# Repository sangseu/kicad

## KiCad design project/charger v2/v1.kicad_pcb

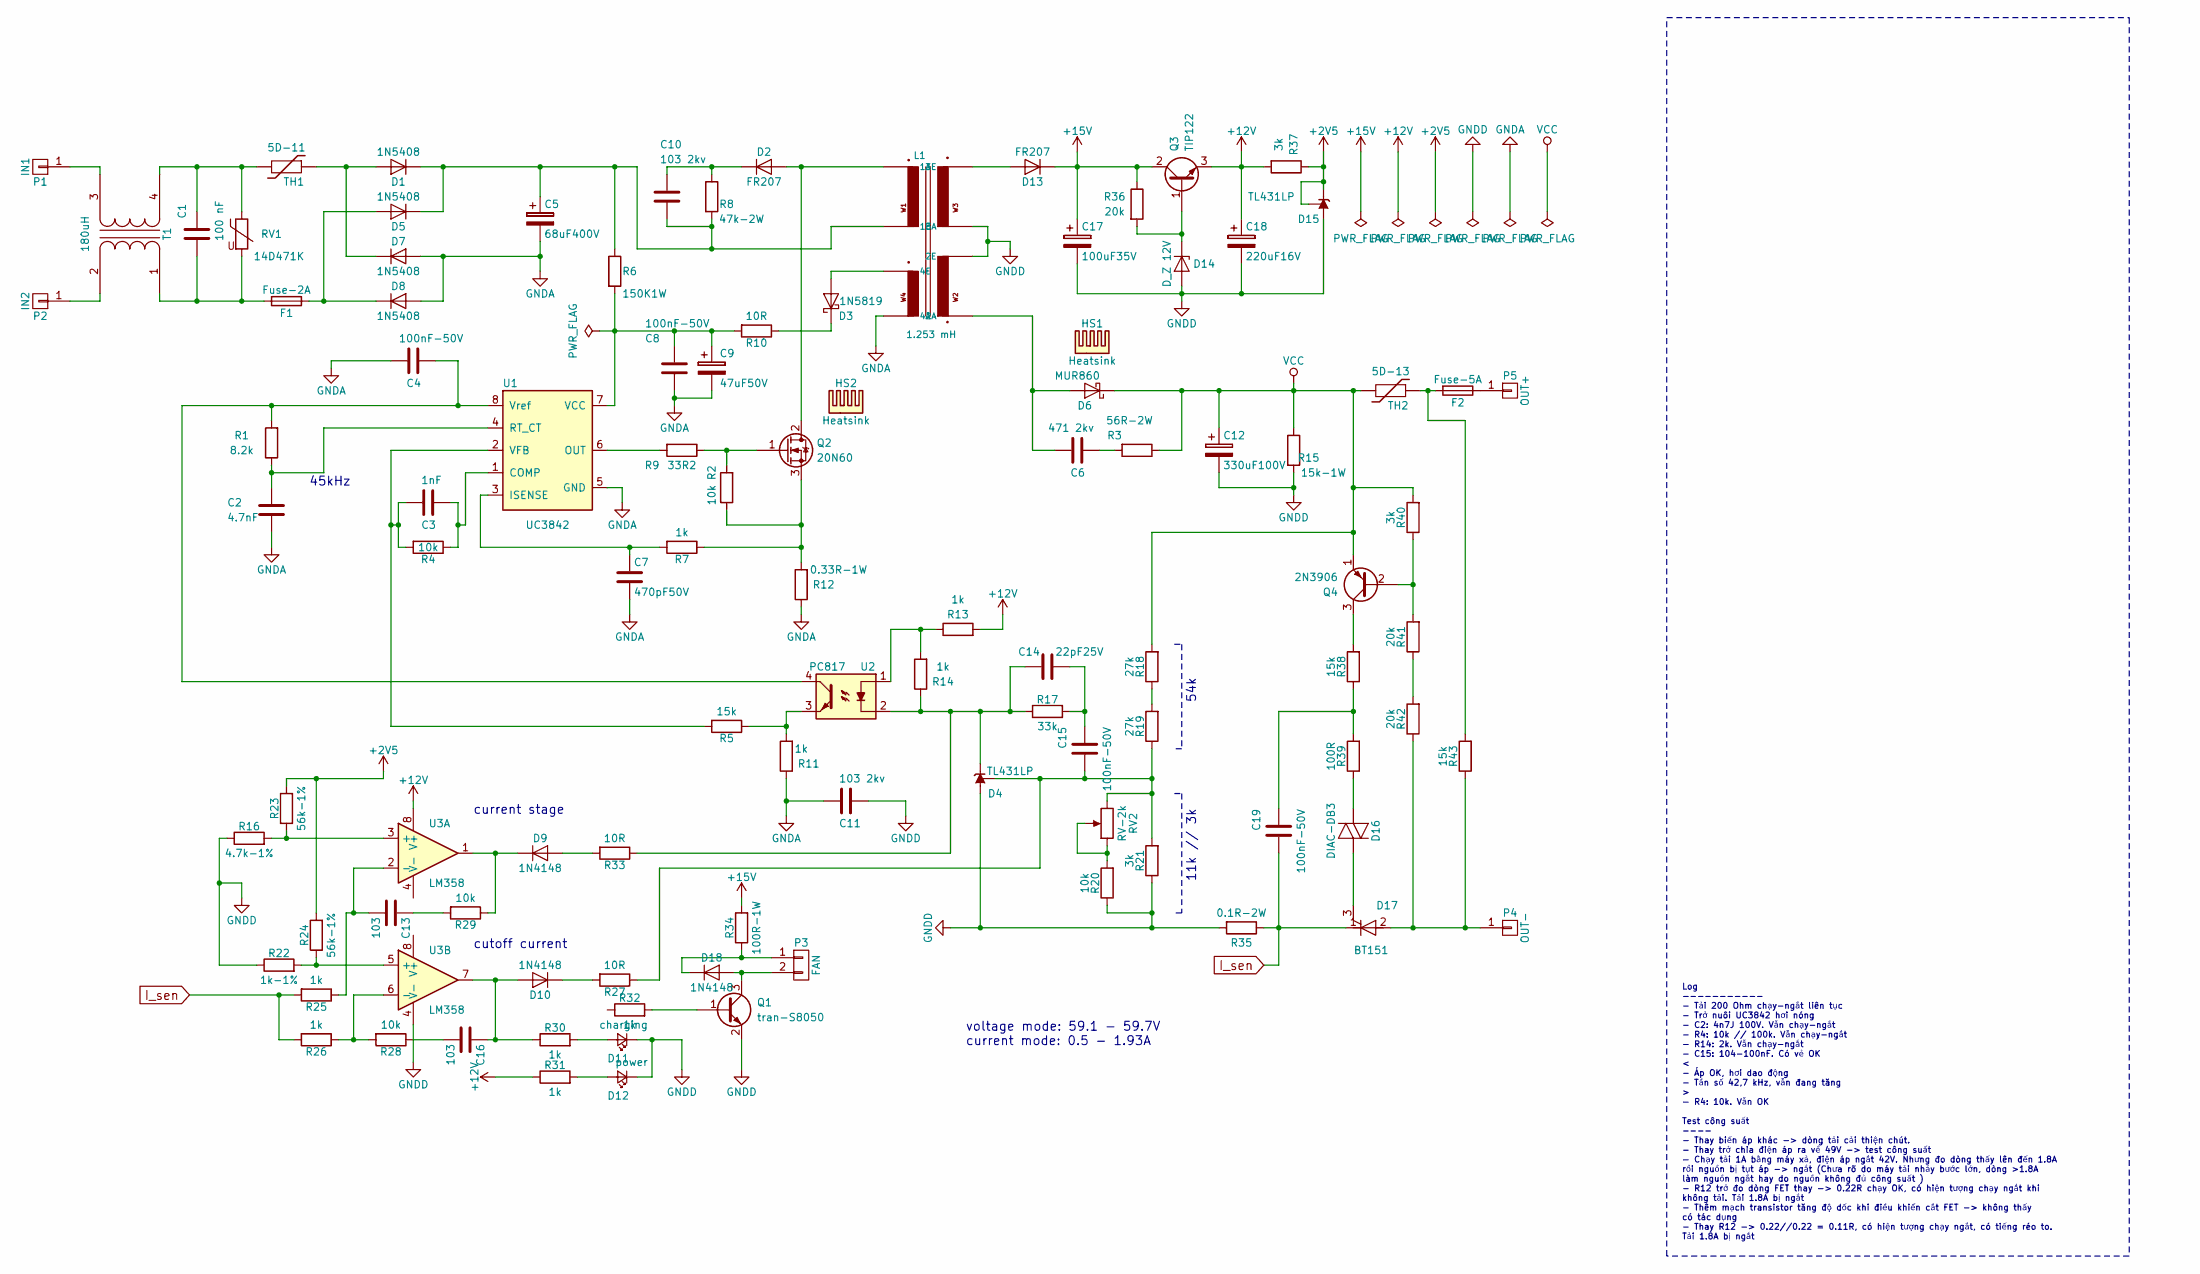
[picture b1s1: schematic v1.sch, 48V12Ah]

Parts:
C1: 100 nF; RV_Disc_D12_W4_P7.5
C2: 4.7nF; C_Rect_L7_W2.5_P5
C3: 1nF; C_0805_HandSoldering
C4, C8, C15, C19: 100nF-50V; C_Rect_L7_W2.5_P5
C5: 68uF400V; C_Radial_D18_L36_P7.5
C6: 471 2kv; C_Rect_L7_W2.5_P5
C7: 470pF50V; C_Rect_L7_W2.5_P5
C9: 47uF50V; C_Radial_D6.3_L11.2_P2.5
C10, C11: 103 2kv; C_Disc_D12_P7.75
C12: 330uF100V; C_Radial_D10_L21_P5
C13, C16: 103; C_Rect_L7_W2.5_P5
C14: 22pF25V; C_0805_HandSoldering
C17: 100uF35V; C_Radial_D6.3_L11.2_P2.5
C18: 220uF16V; C_Radial_D6.3_L11.2_P2.5
D1, D5, D7, D8: 1N5408; Diode_DO-201AD_Horizontal_RM15
D2, D13: FR207; Diode_DO-41_SOD81_Horizontal_RM10
D3: 1N5819; Diode_DO-41_SOD81_Horizontal_RM10
D4, D15: TL431LP; TO-92_Inline_Wide
D6: MUR860; Diode_TO-220_Vertical
D9, D10: 1N4148; Diode_DO-41_SOD81_Horizontal_RM10
D11: charging; LED-5MM
D12: power; LED-5MM
D14: D_Z 12V; Diode_DO-35_SOD27_Horizontal_RM10
D16: DIAC-DB3; Diode_DO-35_SOD27_Horizontal_RM10
D17: BT151; Diode_TO-220_Dual_CommonCathode_Vertical
D18: 1N4148; Diode_DO-41_SOD81_Vertical_AnodeUp
F1: Fuse-2A; Fuseholder5x20_horiz_open_inline_Type-I
F2: Fuse-5A; Fuseholder5x20_horiz_open_inline_Type-I
HS1, HS2: Heatsink; heatsink-D03PA
L1: 1.253 mH; trafo-siemens-RM8-12A
P1: IN1; MountingHole_2.2mm_M2_DIN965_Pad
P2: IN2; MountingHole_2.2mm_M2_DIN965_Pad
P3: FAN; Molex_KK-6410-02_02x2.54mm_Straight
P4: OUT-; MountingHole_2.2mm_M2_DIN965_Pad
P5: OUT+; MountingHole_2.2mm_M2_DIN965_Pad
Q1: tran-S8050; SOT-23
Q2: 20N60; TO-220_Neutral123_Vertical_LargePads
Q3: TIP122; TO-220_Neutral123_Vertical
Q4: 2N3906; TO-92_Inline_Wide
R1: 8.2k; R_0805_HandSoldering
R2, R4, R20, R28, R29: 10k; R_0805_HandSoldering
R3: 56R-2W; Resistor_Horizontal_RM15mm
R5: 15k; R_0805_HandSoldering
R6: 150K1W; Resistor_Horizontal_RM15mm
R7, R13, R25, R26, R30, R31, R32: 1k; Resistor_Horizontal_RM7mm
R8: 47k-2W; Resistor_Horizontal_RM15mm
R9: 33R2; Resistor_Horizontal_RM7mm
R10, R27, R33: 10R; R_0805_HandSoldering
R11, R14: 1k; R_0805_HandSoldering
R12: 0.33R-1W; Resistor_Horizontal_RM15mm
R15: 15k-1W; Resistor_Horizontal_RM15mm
R16: 4.7k-1%; R_0805_HandSoldering
R17: 33k; R_0805_HandSoldering
R18, R19: 27k; Resistor_Horizontal_RM7mm
R21, R40: 3k; R_0805_HandSoldering
R22: 1k-1%; Resistor_Horizontal_RM7mm
R23, R24: 56k-1%; Resistor_Horizontal_RM7mm
R34: 100R-1W; Resistor_Horizontal_RM10mm
R35: 0.1R-2W; Resistor_Horizontal_RM20mm
R36, R41: 20k; R_0805_HandSoldering
R37: 3k; Resistor_Horizontal_RM7mm
R38, R43: 15k; Resistor_Horizontal_RM7mm
R39: 100R; R_0805_HandSoldering
R42: 20k; Resistor_Horizontal_RM7mm
RV1: 14D471K; RV_Disc_D12_W3.9_P7.5
RV2: RV-2k; Potentiometer_Bourns_3296W_3-8Zoll_Inline_ScrewUp
T1: 180uH; inductors-MFE
TH1: 5D-11; R3
TH2: 5D-13; R3
U1: UC3842; DIP-8_W7.62mm_LongPads
U2: PC817; DIP-4_W7.62mm
U3: LM358; DIP-8_W7.62mm_LongPads

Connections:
+2V5: D15.1 (REF), D15.3 (K), R23.2, R24.2, R37.1
+12V: C18.1, Q3.3 (E), R13.2, R31.1, R37.2, U3.8 (V+)
+15V: C17.1, D13.1 (K), Q3.2 (C), R34.2, R36.1
GNDA: C2.2, C4.2, C5.2, C7.2, C8.2, C9.2, C11.2, D7.2 (A), D8.2 (A), L1.6 (4A), R11.1, R12.1, U1.5 (GND)
GNDD: C11.1, C12.2, C17.2, C18.2, D4.2 (A), D11.1 (K), D12.1 (K), D14.2 (A), D15.2 (A), L1.10 (2E), Q1.2 (E), R15.2, R16.1, R20.1, R21.1, R22.1, R35.2, U3.4 (V-)
I_sen: C19.1, D17.1 (K), R25.2, R26.2, R35.1
unnamed: C1.1, RV1.1, T1.4 (SB), TH1.2
unnamed: C1.2, F1.2, RV1.2, T1.1 (AA)
unnamed: C2.1, R1.1, U1.4 (RT_CT)
unnamed: C3.1, R4.1, U1.1 (COMP)
unnamed: C3.2, R4.2, R5.2, U1.2 (VFB)
unnamed: C4.1, R1.2, U1.8 (Vref), U2.4
unnamed: C6.1, R3.2
unnamed: C6.2, D6.2 (A), L1.8 (2A)
unnamed: C7.1, R7.2, U1.3 (ISENSE)
unnamed: C8.1, C9.1, R6.2, R10.2, U1.7 (VCC)
unnamed: C10.1, D2.1 (K), R8.1
unnamed: C5.1, C10.2, D1.1 (K), D5.1 (K), L1.3 (1E), R6.1, R8.2
unnamed: C13.1, R29.2
unnamed: C13.2, R25.1, U3.2 (-)
unnamed: C14.1, C15.2, R17.2
unnamed: C16.2, R28.1
unnamed: C19.2, R38.1, R39.2
unnamed: D1.2 (A), D7.1 (K), TH1.1
unnamed: D2.2 (A), L1.1 (1A), Q2.2 (D)
unnamed: D3.1 (K), R10.1
unnamed: D3.2 (A), L1.5 (4E)
unnamed: D5.2 (A), D8.1 (K), F1.1
unnamed: D9.1 (K), R29.1, U3.1
unnamed: D9.2 (A), R33.2
unnamed: D11.2 (A), R30.2
unnamed: D12.2 (A), R31.2
unnamed: D13.2 (A), L1.12 (3E)
unnamed: D14.1 (K), Q3.1 (B), R36.2
unnamed: D16.1 (K), R39.1
unnamed: D16.2 (A), D17.3 (G)
unnamed: D17.2 (A), P4.1, R42.1, R43.1
unnamed: D18.1 (K), P3.1, R34.1
unnamed: D18.2 (A), P3.2, Q1.3 (C)
unnamed: F2.1, P5.1
unnamed: F2.2, R43.2, TH2.1
unnamed: P1.1, T1.3 (SA)
unnamed: P2.1, T1.2 (AB)
unnamed: Q1.1 (B), R32.2
unnamed: Q2.1 (G), R2.2, R9.1
unnamed: Q2.3 (S), R2.1, R7.1, R12.2
unnamed: Q4.2 (B), R40.1, R41.2
unnamed: Q4.3 (C), R38.2
unnamed: R9.2, U1.6 (OUT)
unnamed: R5.1, R11.2, U2.3
unnamed: R13.1, R14.2, U2.1
unnamed: R16.2, R23.1, U3.3 (+)
unnamed: R18.1, R19.2
unnamed: R20.2, RV2.1, RV2.2
unnamed: R22.2, R24.1, U3.5 (+)
unnamed: R26.1, R28.2, U3.6 (-)
unnamed: R41.1, R42.2
VCC: C12.1, D6.1 (K), Q4.1 (E), R3.1, R15.1, R18.2, R40.2, TH2.2

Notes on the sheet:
voltage mode: 59.1 - 59.7V current mode: 0.5 - 1.93A
45kHz
current stage
cutoff current
54k
11k // 3k
Log ----------- - Tải 200 Ohm chạy-ngắt liên tục - Trở nuôi UC3842 hơi nóng - C2: 4n7J 100V. Vẫn chạy-ngắt - R4: 10k // 100k. Vẫn chạy-ngắt - R14: 2k. Vẫn chạy-ngắt - C15: 104-100nF. Có vẻ OK < - Áp OK, hơi dao động - Tần số 42,7 kHz, vẫn đang tăng > - R4: 10k. Vẫn OK Test công suất ---- - Thay biế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

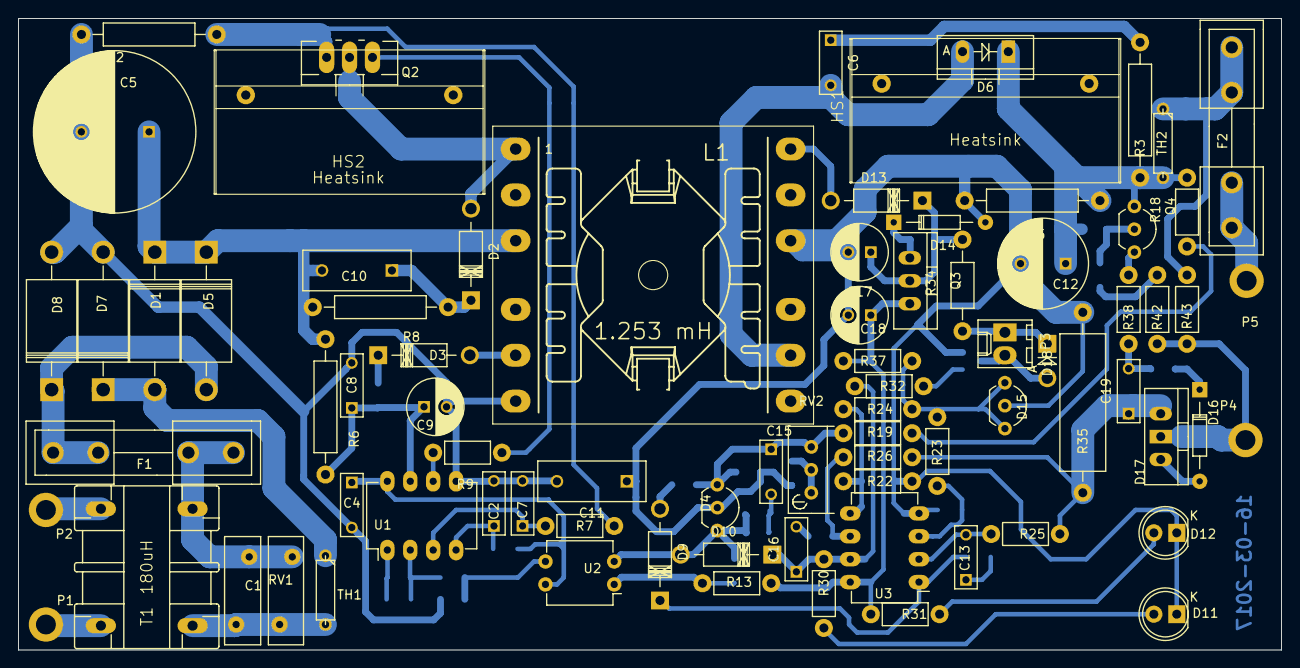
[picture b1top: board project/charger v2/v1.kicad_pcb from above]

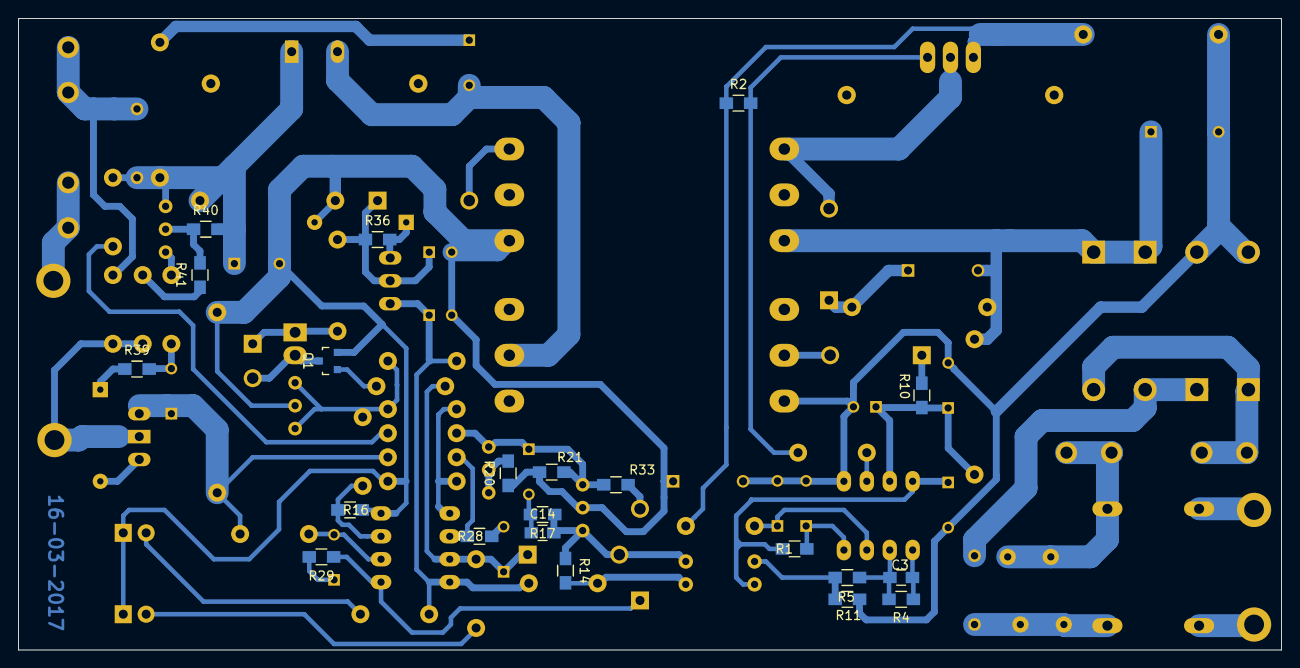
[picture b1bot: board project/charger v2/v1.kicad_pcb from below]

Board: 2 copper layers, 140.0 x 70.0 mm, 101 parts (21 on the bottom side), 61 nets.

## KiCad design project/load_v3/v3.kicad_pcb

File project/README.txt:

log
===
1. chager v1: so cap, phan hoi dien ap dung thong so. Mach dieu khien dong sac, dieu khien ngat sac SAI
2. 48V-1A: chay OK nhow su giup so cua anh Toan
3. 48V-2A. 48V-3A SAI

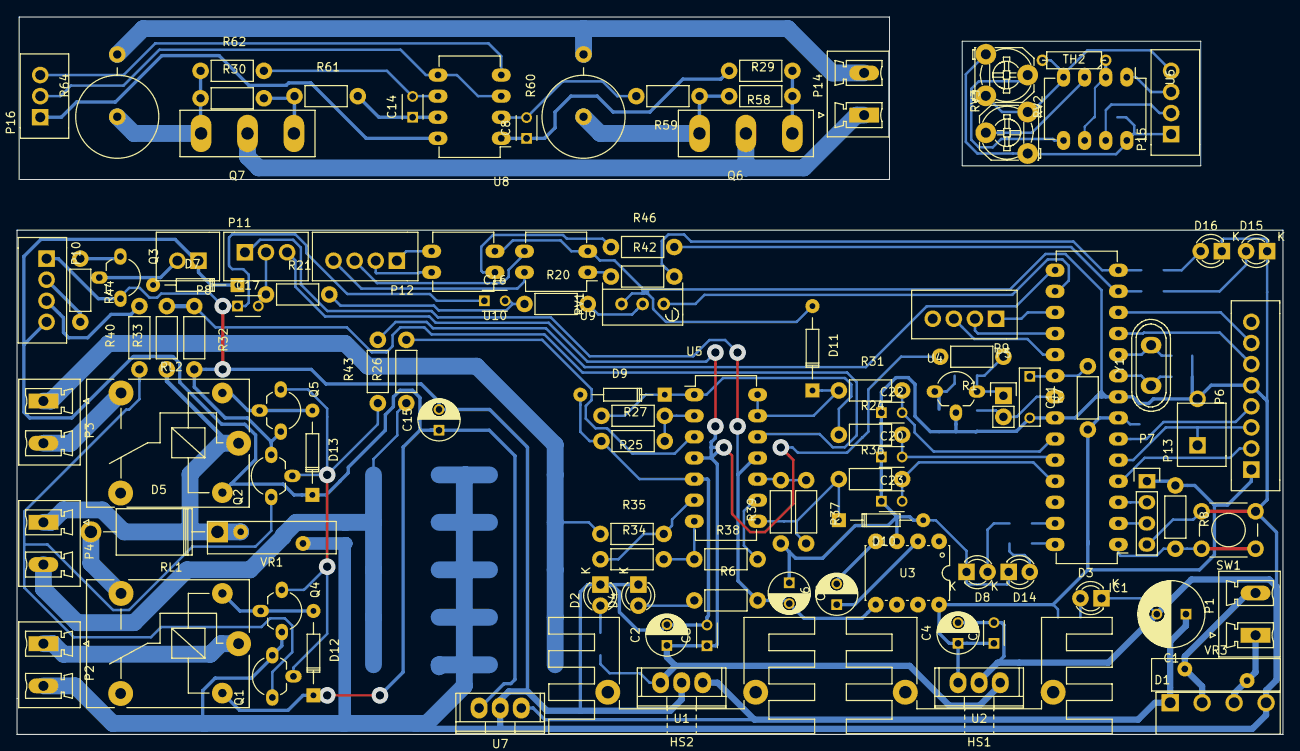
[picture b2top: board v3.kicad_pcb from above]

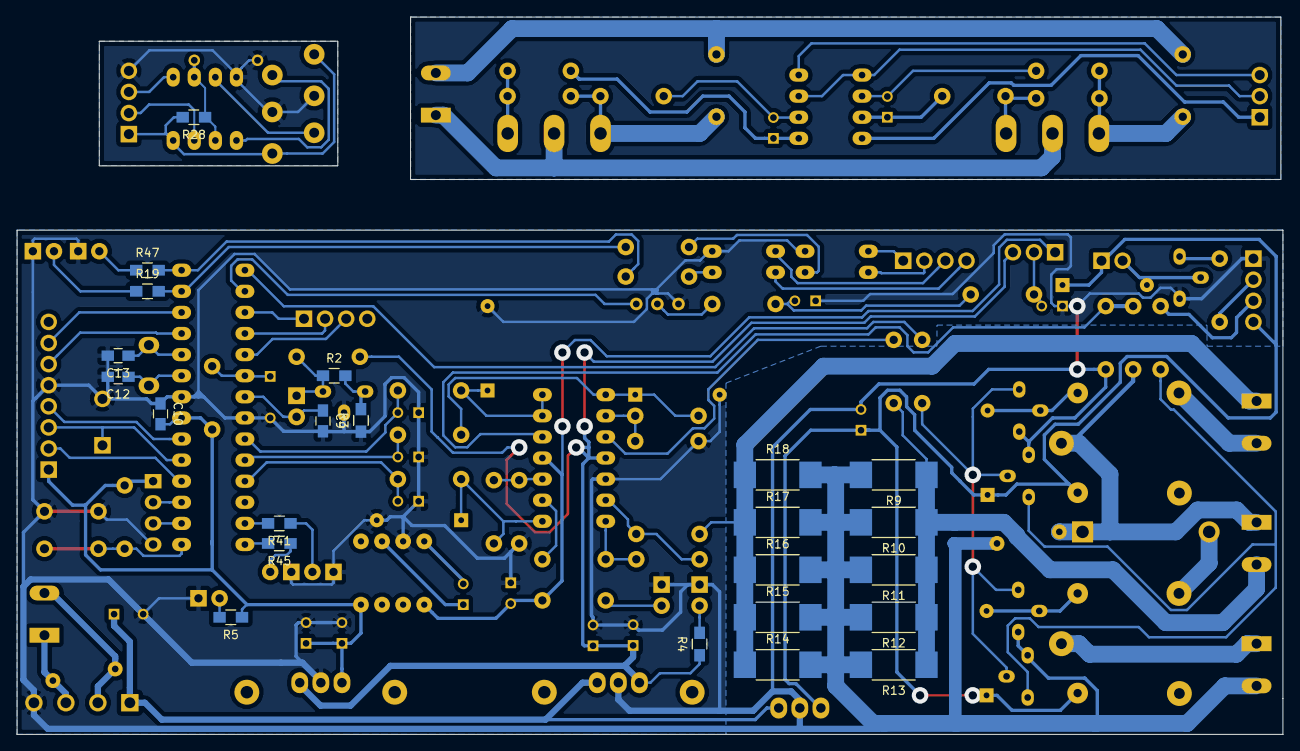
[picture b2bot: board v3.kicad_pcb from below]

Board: 2 copper layers, 152.4 x 60.7 mm, 132 parts (23 on the bottom side), 87 nets.

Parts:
C1: 220uF-50V; C_Radial_D8_L11.5_P3.5
C2, C15: 220F-25V; C_Radial_D5_L6_P2.5
C3, C5, C16, C17, C20, C22, C23: 100nF; C_Disc_D3_P2.5
C4: 470uF-25V; C_Radial_D5_L6_P2.5
C6, C7: 10uF-25V; C_Radial_D5_L6_P2.5
C8, C14: 22nF; C_Disc_D3_P2.5
C9, C10: 100nF; C_0805_HandSoldering
C11: 100nF; C_Rect_L7_W2.5_P5
C12, C13: 22pF; C_0805_HandSoldering
D1: Diode_Bridge; Diode_Bridge_KBP206
D2, D3, D4, D8, D14, D15, D16: Led_Small; LED-3MM
D5: 1N5402; Diode_DO-201AD_Horizontal_RM15
D7: 1N4001; Diode_DO-35_SOD27_Horizontal_RM10
D9, D10, D11: 5.1V; Diode_DO-35_SOD27_Horizontal_RM10
D12, D13: 4001; Diode_DO-35_SOD27_Horizontal_RM10
HS1, HS2: HEATSINK; Heatsink_Stonecold_HS-132_32x14mm_2xFixation1.5mm
IC1: ATMEGA328-P; DIP-28_W7.62mm_LongPads
P1: 12VAC; PhoenixContact_MCV-G_02x5.08mm_Vertical
P2: NGUON; PhoenixContact_MCV-G_02x5.08mm_Vertical
P3: SAC; PhoenixContact_MCV-G_02x5.08mm_Vertical
P4: DS; PhoenixContact_MCV-G_02x5.08mm_Vertical
P5: CONN_01X02; Pin_Header_Straight_1x02
P6: button; XH2.54-8P
P7: UART; Pin_Header_Straight_1x04
P8: FAN; XH2.54-2P
P9: 7-seg; XH2.54-4P
P10, P15: overheat; XH2.54-4P
P11: G; XH2.54-3P
P12: opto; XH2.54-4P
P13: tac_auto; XH2.54-2P
P14: pwr; PhoenixContact_MCV-G_02x5.08mm_Vertical
P16: g; XH2.54-3P
Q1, Q2, Q3: Q_NPN_BCE; TO-92_Molded_Wide_Oval_Reverse
Q4, Q5: 2n222; TO-92_Molded_Wide_Oval_Reverse
Q6, Q7: Q_NMOS_GDS; TO-247_Vertical_Neutral123
R1, R27, R39, R42, R43, R46, R59, R62: 1k; Resistor_Horizontal_RM7mm
R2, R3, R28: 10k; R_0805_HandSoldering
R4: 1k; R_0805_HandSoldering
R5, R19, R41, R45, R47: 470R; R_0805_HandSoldering
R6, R40, R44, R58, R61: 470R; Resistor_Horizontal_RM7mm
R7: 10uH; Resistor_Horizontal_RM7mm
R8, R20, R21, R26, R29, R30, R32, R34, R35, R38: 10k; Resistor_Horizontal_RM7mm
R9, R10, R11, R12, R13, R14, R15, R16, R17, R18: 0.5R; R_2512_HandSoldering
R24, R31, R36: 330R; Resistor_Horizontal_RM7mm
R25, R37: 8.2k; Resistor_Horizontal_RM7mm
R33: 180k; Resistor_Horizontal_RM7mm
R60, R64: 0.5R; Resistor_Vertical_RM7.5mm
RL1: onN; Relay_SANYOU_SRD_Series_Form_C
RL2: onS; Relay_SANYOU_SRD_Series_Form_C
RV1: 10k; Potentiometer_Bourns_3296W_3-8Zoll_Inline_ScrewUp
RV2, RV3: 20k; Potentiometer_Triwood_RM-065
SW1: reset; SW_PUSH_6mm
TH2: Thermistor; R3
U1, U7: LM7812CT; TO-220
U2: LM7805CT; TO-220
U3: ICL7660; PDIP-8
U4: TL431; TO-92_Molded_Wide_Oval_Reverse
U5: LM324N; DIP-14_W7.62mm_LongPads
U6, U8: LM358; DIP-8_W7.62mm_LongPads
U9, U10: PC817; DIP-4_W7.62mm_LongPads
VR1, VR3: 14D180V; RV_Disc_D15.5_W3.9_P7.5
Y1: 16MHz; Crystal_HC50-U_Vertical

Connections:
12Vrelay: C15.1, D7.1, D12.1, D13.1, P8.1, P10.4, P15.1, R28.2, RL1.5, RL2.5, RV2.1, RV3.1, U6.8, U7.3
17V: C1.1, D1.3, U1.1, U7.1
+5V: C4.1, C5.1, C10.2, IC1.7, P6.1, P7.1, R5.1, R7.1, R8.1, U2.3, U3.8
+12V: C2.1, C3.1, P11.3, P16.1, R1.2, R4.1, U1.3, U2.1, U5.4, U8.8
-5V: C7.2, P11.1, P16.3, R6.2, U3.5, U5.11, U8.4
D: D5.1, P4.1, P14.1, Q6.2, Q7.2, R33.1, RL2.1, VR1.1
G: C17.2, P11.2, P16.2, R21.1, U8.3, U8.5
N+: P2.1, RL1.1
N-: C1.2, C2.2, C3.2, C4.2, C5.2, C7.1, C9.2, C10.1, C11.2, C12.2, C13.2, C15.2, C16.1, C17.1, C20.1, C22.1, C23.1, D1.1, D2.1, D3.1, D4.1, D8.1, D9.2, D10.2, D11.2, D14.1, D15.1, D16.1, IC1.8, IC1.22, P2.2, P6.5, P7.4, P10.1, P13.2, P15.4, Q1.3, Q2.3, Q3.3, Q4.3, Q5.3, R3.1, R9.2, R10.2, R11.2, R12.2, R13.2, R14.2, R15.2, R16.2, R17.2, R18.2, R27.1, R32.2, R39.1, RV1.3, RV2.3, RV3.3, SW1.2, TH2.2, U1.2, U2.2, U3.3, U4.2, U5.5, U6.4, U7.2, U9.2, U10.2, VR1.2
unnamed: C6.1, U3.2
unnamed: C6.2, U3.4
unnamed: C8.1, R58.2, U8.1
unnamed: C8.2, R59.2, U8.2
unnamed: C11.1, IC1.20, R7.2
unnamed: C12.1, IC1.9, Y1.1
unnamed: C13.1, IC1.10, Y1.2
unnamed: C14.1, R61.2, U8.7
unnamed: C14.2, R62.2, U8.6
unnamed: C16.2, R20.1, R21.2
unnamed: D1.2, P1.2, VR3.2
unnamed: D1.4, P1.1, VR3.1
unnamed: D2.2, R4.2
unnamed: D3.2, R5.2
unnamed: D4.2, R6.1
unnamed: D7.2, P8.2, Q3.2
unnamed: D8.2, R41.1
unnamed: D9.1, R24.1, R25.2, U5.1
unnamed: D10.1, R36.1, R37.2, U5.8
unnamed: D11.1, R31.1, U5.13, U5.14
unnamed: D12.2, Q4.2, RL1.2
unnamed: D13.2, Q5.2, RL2.2
unnamed: D14.2, R45.1
unnamed: D15.2, R19.1
unnamed: D16.2, R47.1
unnamed: IC1.1, R8.2, SW1.1
unnamed: IC1.15, R43.2
unnamed: P5.1, R1.1, R2.1, U4.3
unnamed: P12.1, U10.3
unnamed: P12.2, U10.4
unnamed: P12.3, U9.3
unnamed: P12.4, U9.4
unnamed: Q1.1, Q2.1, R40.1
unnamed: Q3.1, R44.1
unnamed: Q6.1, R29.2, R58.1
unnamed: Q6.3, R29.1, R59.1, R60.1
unnamed: Q7.1, R30.2, R61.1
unnamed: Q7.3, R30.1, R62.1, R64.1
unnamed: R2.2, R3.2, U4.1
unnamed: R20.2, RV1.2
unnamed: R25.1, R27.2, U5.2
unnamed: R26.2, U5.3
unnamed: R28.1, TH2.1, U6.2, U6.6
unnamed: R32.1, R33.2, U5.12
unnamed: R34.1, R35.2, U5.6
unnamed: R34.2, R38.1, U5.7
unnamed: R37.1, R39.2, U5.10
unnamed: R38.2, U5.9
unnamed: RV2.2, U6.5
unnamed: RV3.2, U6.3
RX: IC1.2, P7.3
S: P4.2, P14.2, R9.1, R10.1, R11.1, R12.1, R13.1, R26.1, R60.2, R64.2
S+: P3.2, RL2.3
S-: P3.1, R14.1, R15.1, R16.1, R17.1, R18.1, R35.1
TX: IC1.3, P7.2
Vref: C9.1, IC1.21, P5.2
buzz: IC1.12, P6.7
down: IC1.11, P6.6
fail: IC1.28, R45.2
l_auto: IC1.13, R19.2, R46.2
l_start: IC1.14, R42.2, R47.2
off: P10.3, P15.2, R40.2, U6.7
ok: IC1.27, R41.2
onFan: P10.2, P15.3, R44.2, U6.1
onN: Q1.2, Q2.2, Q4.1, Q5.1, R43.1
opto_auto: R46.1, U10.1
opto_start: R42.1, U9.1
pwm: IC1.16, RV1.1
rN+: D5.2, RL1.3
rck: IC1.19, P9.3
scr: IC1.18, P9.2
senIN: C20.2, IC1.24, R24.2
senIS: C23.2, IC1.25
senUS: C22.2, IC1.23, R31.2
ser: IC1.17, P9.1
start: IC1.5, P6.3, P13.1
stop: IC1.4, P6.2
up: IC1.6, P6.4

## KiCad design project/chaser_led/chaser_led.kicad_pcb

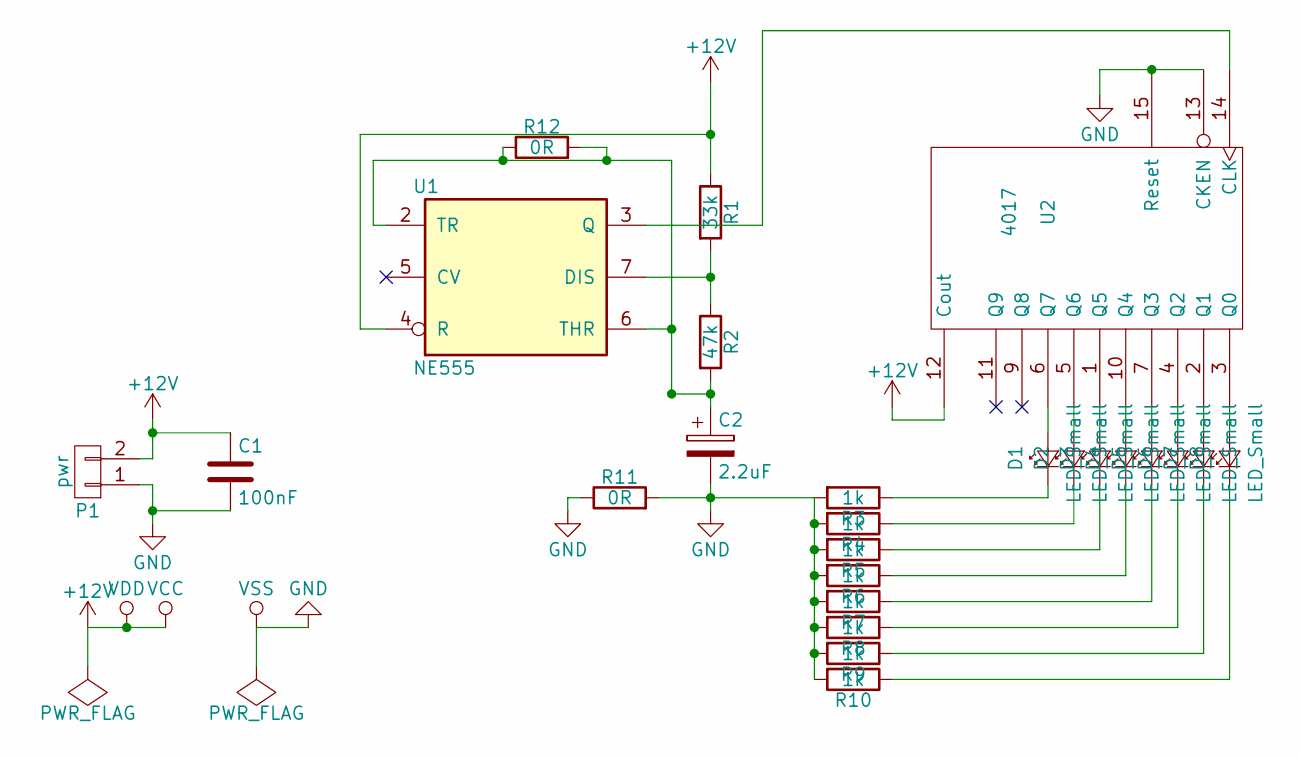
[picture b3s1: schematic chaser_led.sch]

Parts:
C1: 100nF; C_Disc_D3_P2.5
C2: 2.2uF; C_Radial_D5_L6_P2.5
D1, D2, D3, D4, D5, D6, D7, D8: LED_Small; LED-3MM
P1: pwr; AK300-2
R1: 33k; Resistor_Horizontal_RM7mm
R2: 47k; Resistor_Horizontal_RM7mm
R3, R4, R5, R6, R7, R8, R9, R10: 1k; Resistor_Horizontal_RM7mm
R11, R12: 0R; WireConnection_0.80mmDrill
U1: NE555; SOIC-8-N
U2: 4017; SO-16-N

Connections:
+12V: C1.1, P1.2, R1.1, U1.4 (R), U1.8 (VCC), U2.12 (Cout), U2.16 (VDD)
GND: C1.2, C2.2, P1.1, R3.2, R4.2, R5.2, R6.2, R7.2, R8.2, R9.2, R10.2, R11.1, R11.2, U1.1 (GND), U2.8 (VSS), U2.13 (CKEN), U2.15 (Reset)
unnamed: C2.1, R2.2, R12.1, R12.2, U1.2 (TR), U1.6 (THR)
unnamed: D1.1 (K), R3.1
unnamed: D1.2 (A), U2.6 (Q7)
unnamed: D2.1 (K), R4.1
unnamed: D2.2 (A), U2.5 (Q6)
unnamed: D3.1 (K), R5.1
unnamed: D3.2 (A), U2.1 (Q5)
unnamed: D4.1 (K), R6.1
unnamed: D4.2 (A), U2.10 (Q4)
unnamed: D5.1 (K), R7.1
unnamed: D5.2 (A), U2.7 (Q3)
unnamed: D6.1 (K), R8.1
unnamed: D6.2 (A), U2.4 (Q2)
unnamed: D7.1 (K), R9.1
unnamed: D7.2 (A), U2.2 (Q1)
unnamed: D8.1 (K), R10.1
unnamed: D8.2 (A), U2.3 (Q0)
unnamed: R1.2, R2.1, U1.7 (DIS)
unnamed: U1.3 (Q), U2.14 (CLK)

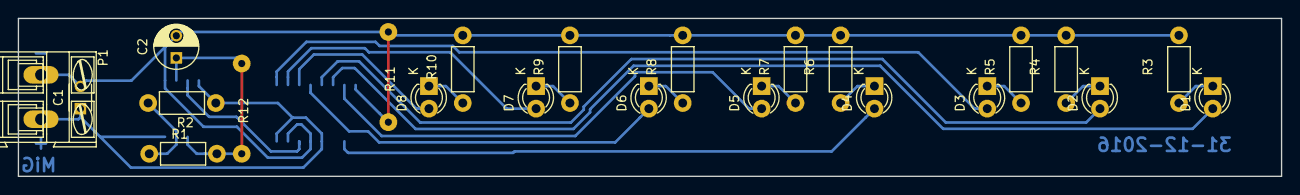
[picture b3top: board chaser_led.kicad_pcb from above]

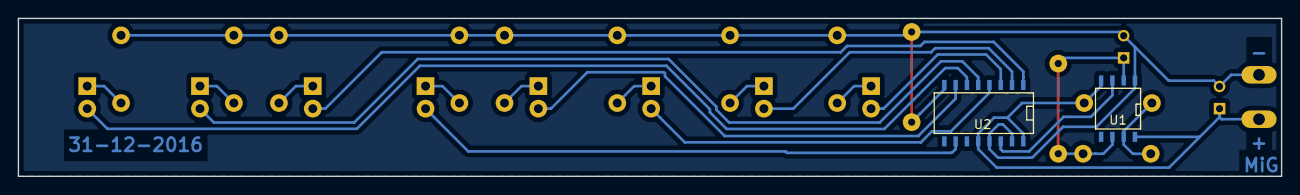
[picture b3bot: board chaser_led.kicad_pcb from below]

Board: 2 copper layers, 142.2 x 17.8 mm, 25 parts (2 on the bottom side), 21 nets.

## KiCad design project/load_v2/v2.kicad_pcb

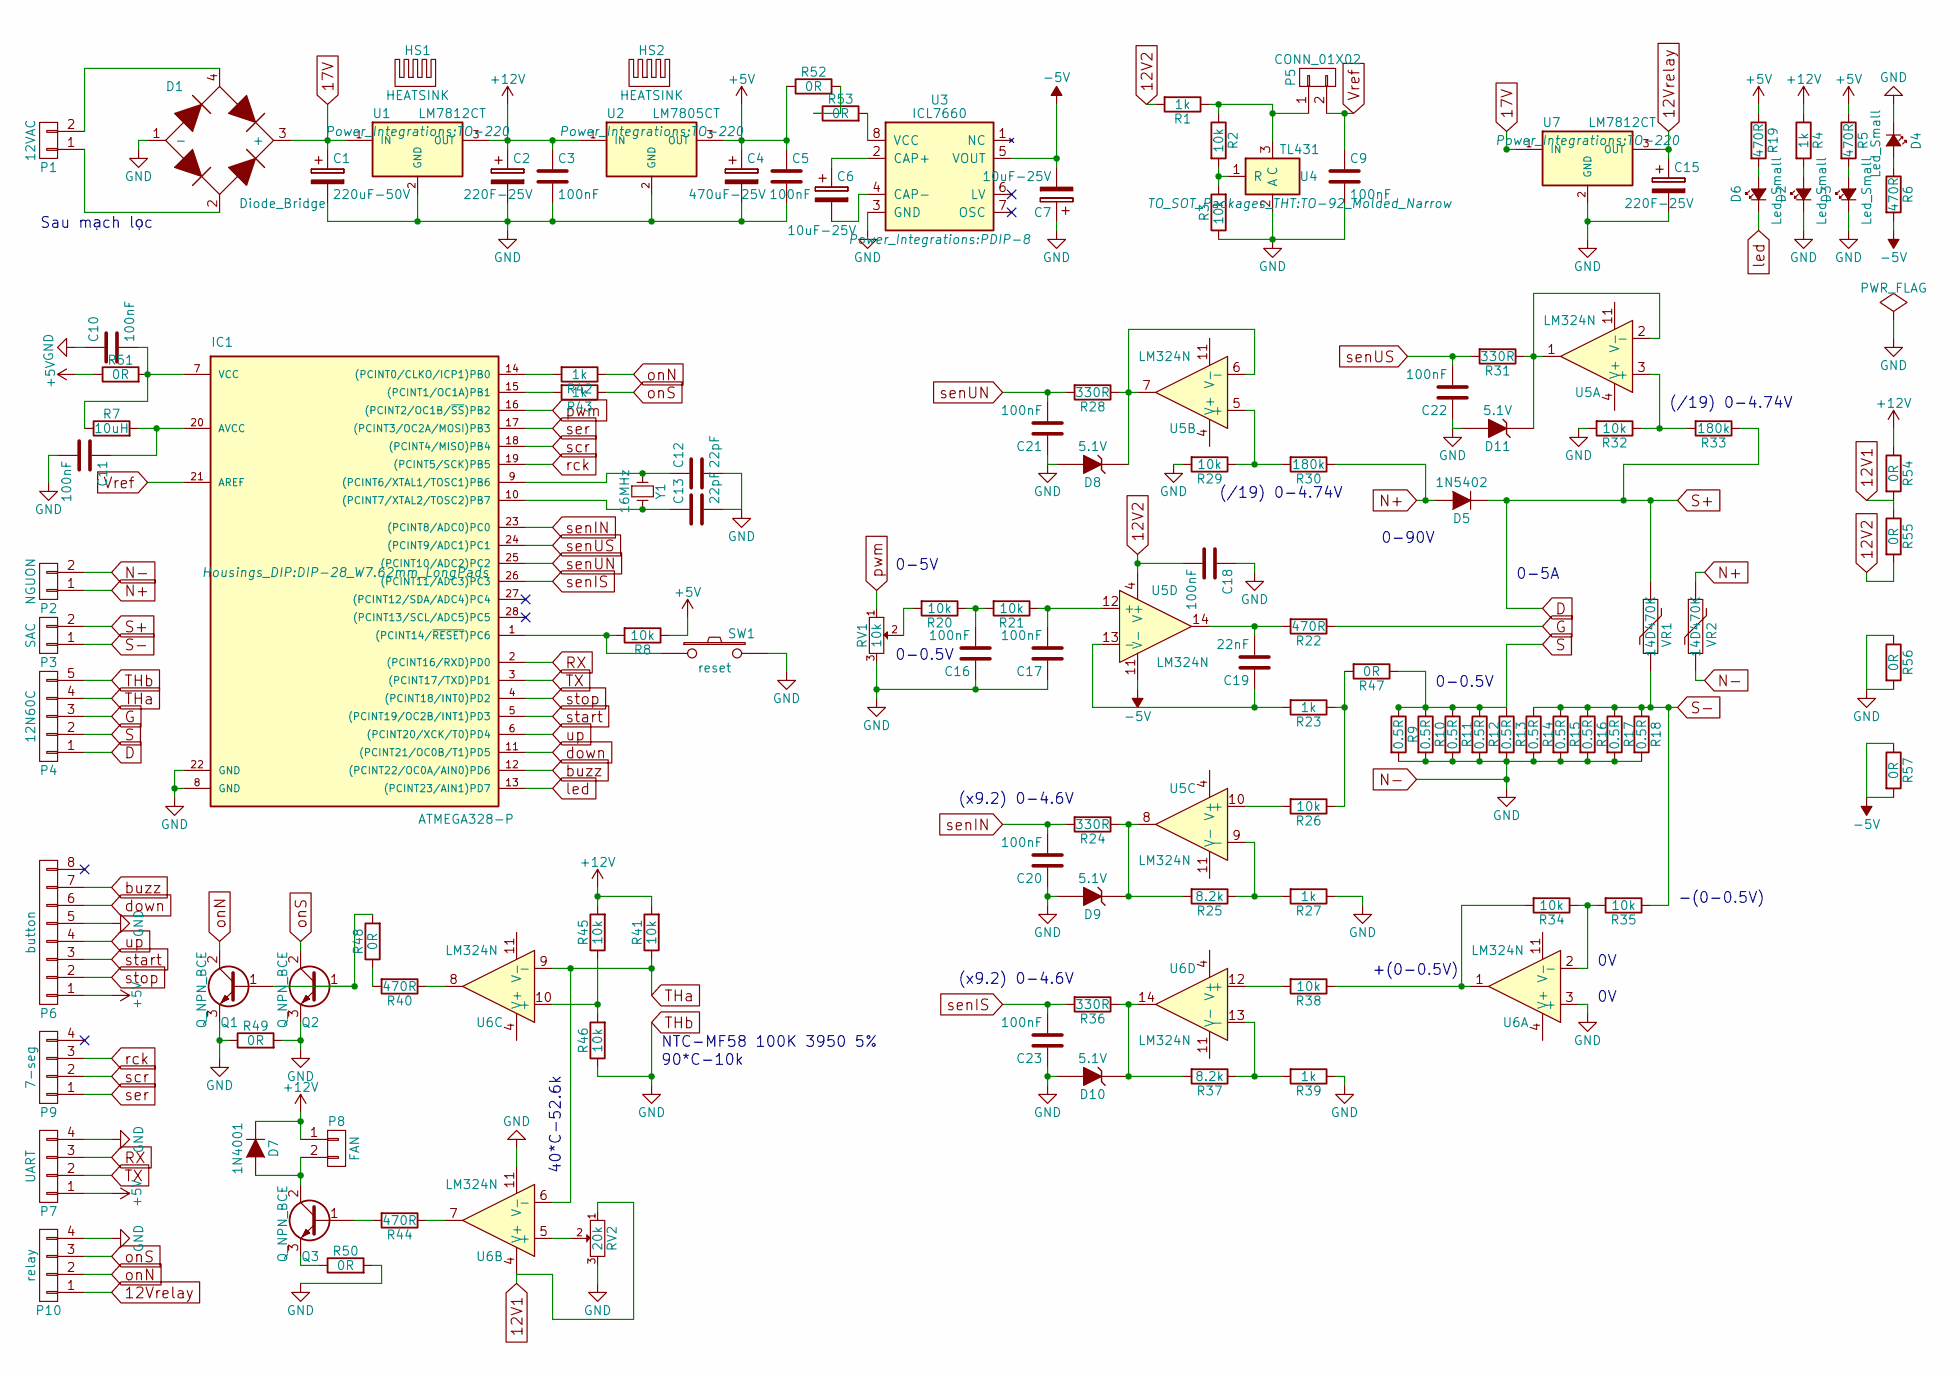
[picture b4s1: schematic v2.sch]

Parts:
C1: 220uF-50V; C_Radial_D5_L6_P2.5
C2, C15: 220F-25V; C_Radial_D5_L6_P2.5
C3, C5, C16, C17, C20, C21, C22, C23: 100nF; C_Disc_D3_P2.5
C4: 470uF-25V; C_Radial_D5_L6_P2.5
C6, C7: 10uF-25V; C_Radial_D5_L6_P2.5
C9, C10: 100nF; C_0805_HandSoldering
C11: 100nF; C_Rect_L7_W2.5_P5
C12, C13: 22pF; C_0805_HandSoldering
C18: 100nF; C_Rect_L7_W2_P5
C19: 22nF; C_Disc_D3_P2.5
D1: Diode_Bridge; Diode_Bridge_18.5x5.5
D2, D3, D4, D6: Led_Small; LED-3MM
D5: 1N5402; Diode_DO-201AD_Horizontal_RM15
D7: 1N4001; Diode_DO-35_SOD27_Horizontal_RM10
D8, D9, D10, D11: 5.1V; Diode_DO-35_SOD27_Horizontal_RM10
HS1, HS2: HEATSINK; Heatsink_Stonecold_HS-132_32x14mm_2xFixation1.5mm
IC1: ATMEGA328-P; DIP-28_W7.62mm_LongPads
P1: 12VAC; PhoenixContact_MCV-G_02x5.08mm_Vertical
P2: NGUON; PhoenixContact_MCV-G_02x5.08mm_Vertical
P3: SAC; PhoenixContact_MCV-G_02x5.08mm_Vertical
P4: 12N60C; PhoenixContact_MCV-G_05x5.08mm_Vertical
P5: CONN_01X02; Pin_Header_Straight_1x02
P6: button; XH2.54-8P
P7: UART; Pin_Header_Straight_1x04
P8: FAN; XH2.54-2P
P9: 7-seg; XH2.54-4P
P10: relay; XH2.54-4P
Q1, Q2, Q3: Q_NPN_BCE; TO-92_Molded_Narrow
R1, R4, R23, R27, R39, R42, R43: 1k; Resistor_Horizontal_RM7mm
R2, R3: 10k; R_0805_HandSoldering
R5, R6, R19, R22, R40, R44: 470R; Resistor_Horizontal_RM7mm
R7: 10uH; Resistor_Horizontal_RM7mm
R8, R20, R21, R26, R32, R34, R35, R38, R41, R45, R46: 10k; Resistor_Horizontal_RM7mm
R9, R10, R11, R12, R13, R14, R15, R16, R17, R18: 0.5R; R_2512_HandSoldering
R24, R28, R31, R36: 330R; Resistor_Horizontal_RM7mm
R25, R37: 8.2k; Resistor_Horizontal_RM7mm
R29: 10k; Resistor_Horizontal_RM15mm
R30: 180k; Resistor_Horizontal_RM15mm
R33: 180k; Resistor_Horizontal_RM7mm
R47, R48, R49, R50, R51, R52, R53, R54, R55, R56, R57: 0R; WireConnection_0.80mmDrill
RV1: 10k; Potentiometer_Bourns_3296W_3-8Zoll_Inline_ScrewUp
RV2: 20k; Potentiometer_Bourns_3296W_3-8Zoll_Inline_ScrewUp
SW1: reset; SW_PUSH_6mm
U1, U7: LM7812CT; TO-220
U2: LM7805CT; TO-220
U3: ICL7660; PDIP-8
U4: TL431; TO-92_Molded_Narrow
U5, U6: LM324N; DIP-14_W7.62mm_LongPads
VR1, VR2: 14D470K; RV_Disc_D15.5_W3.9_P7.5
Y1: 16MHz; Crystal_HC52-U_Vertical

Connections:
12V1: R54.2, R55.1, RV2.1, U6.4 (V+)
12V2: C18.2, R1.2, R55.2, U5.4 (V+)
12Vrelay: C15.1, P10.1, U7.3 (OUT)
17V: C1.1, D1.3 (+), U1.1 (IN), U7.1 (IN)
+5V: C4.1, C5.1, P6.1, P7.1, R5.1, R8.1, R19.1, R51.1, R52.1, U2.3 (OUT)
+12V: C2.1, C3.1, D7.1 (K), P8.1, R4.1, R41.2, R45.2, R54.1, U1.3 (OUT), U2.1 (IN)
-5V: C7.2, R6.2, R57.1, R57.2, U3.5 (VOUT), U5.11 (V-)
D: D5.1 (K), P3.2, P4.1, R33.1, VR1.1
G: P4.3, R22.1
N+: D5.2 (A), P2.1, R30.1, VR2.1
N-: C1.2, C2.2, C3.2, C4.2, C5.2, C7.1, C9.2, C10.1, C11.2, C12.2, C13.2, C15.2, C16.1, C17.1, C18.1, C20.1, C21.1, C22.1, C23.1, D1.1 (-), D2.1 (K), D3.1 (K), D4.1 (K), D8.2 (A), D9.2 (A), D10.2 (A), D11.2 (A), IC1.8 (GND), IC1.22 (GND), P2.2, P4.5, P6.5, P7.4, P10.4, Q1.3 (E), Q2.3 (E), R3.1, R9.2, R10.2, R11.2, R12.2, R13.2, R14.2, R15.2, R16.2, R17.2, R18.2, R27.1, R29.2, R32.2, R39.1, R46.1, R49.1, R49.2, R50.2, R56.1, R56.2, RV1.3, RV2.3, SW1.2, U1.2 (GND), U2.2 (GND), U3.3 (GND), U4.2 (A), U6.3 (+), U6.11 (V-), U7.2 (GND), VR2.2
unnamed: C6.1, U3.2 (CAP+)
unnamed: C6.2, U3.4 (CAP-)
unnamed: C10.2, IC1.7 (VCC), R7.1, R51.2
unnamed: C11.1, IC1.20 (AVCC), R7.2
unnamed: C12.1, IC1.9 ((PCINT6/XTAL1/TOSC1)PB6), Y1.1
unnamed: C13.1, IC1.10 ((PCINT7/XTAL2/TOSC2)PB7), Y1.2
unnamed: C16.2, R20.1, R21.2
unnamed: C17.2, R21.1, U5.12 (+)
unnamed: C19.1, R23.2, U5.13 (-)
unnamed: C19.2, R22.2, U5.14
unnamed: D1.2, P1.1
unnamed: D1.4, P1.2
unnamed: D2.2 (A), R4.2
unnamed: D3.2 (A), R5.2
unnamed: D4.2 (A), R6.1
unnamed: D6.2 (A), R19.2
unnamed: D7.2 (A), P8.2, Q3.2 (C)
unnamed: D8.1 (K), R28.1, U5.6 (-), U5.7
unnamed: D9.1 (K), R24.1, R25.2, U5.8
unnamed: D10.1 (K), R36.1, R37.2, U6.14
unnamed: D11.1 (K), R31.1, U5.1, U5.2 (-)
unnamed: IC1.1 ((PCINT14/~RESET~)PC6), R8.2, SW1.1
unnamed: IC1.14 ((PCINT0/CLKO/ICP1)PB0), R42.2
unnamed: IC1.15 ((PCINT1/OC1A)PB1), R43.2
unnamed: P5.1, R1.1, R2.1, U4.3 (C)
unnamed: Q1.1 (B), Q2.1 (B), R48.2
unnamed: Q3.1 (B), R44.2
unnamed: Q3.3 (E), R50.1
unnamed: R2.2, R3.2, U4.1 (R)
unnamed: R20.2, RV1.2
unnamed: R23.1, R26.1, R47.2
unnamed: R25.1, R27.2, U5.9 (-)
unnamed: R26.2, U5.10 (+)
unnamed: R29.1, R30.2, U5.5 (+)
unnamed: R32.1, R33.2, U5.3 (+)
unnamed: R34.1, R35.2, U6.2 (-)
unnamed: R34.2, R38.1, U6.1
unnamed: R37.1, R39.2, U6.13 (-)
unnamed: R38.2, U6.12 (+)
unnamed: R40.1, U6.8
unnamed: R40.2, R48.1
unnamed: R44.1, U6.7
unnamed: R45.1, R46.2, U6.10 (+)
unnamed: R52.2, R53.1
unnamed: R53.2, U3.8 (VCC)
unnamed: RV2.2, U6.5 (+)
RX: IC1.2 ((PCINT16/RXD)PD0), P7.3
S: P4.2, R9.1, R10.1, R11.1, R12.1, R13.1, R47.1
S-: P3.1, R14.1, R15.1, R16.1, R17.1, R18.1, R35.1, VR1.2
THa: P4.4, R41.1, U6.6 (-), U6.9 (-)
TX: IC1.3 ((PCINT17/TXD)PD1), P7.2
Vref: C9.1, IC1.21 (AREF), P5.2
buzz: IC1.12 ((PCINT22/OC0A/AIN0)PD6), P6.7
down: IC1.11 ((PCINT21/OC0B/T1)PD5), P6.6
led: D6.1 (K), IC1.13 ((PCINT23/AIN1)PD7)
onN: P10.2, Q1.2 (C), R42.1
onS: P10.3, Q2.2 (C), R43.1
pwm: IC1.16 ((PCINT2/OC1B/~SS~)PB2), RV1.1
rck: IC1.19 ((PCINT5/SCK)PB5), P9.3
scr: IC1.18 ((PCINT4/MISO)PB4), P9.2
senIN: C20.2, IC1.23 ((PCINT8/ADC0)PC0), R24.2
senIS: C23.2, IC1.26 ((PCINT11/ADC3)PC3), R36.2
senUN: C21.2, IC1.25 ((PCINT10/ADC2)PC2), R28.2
senUS: C22.2, IC1.24 ((PCINT9/ADC1)PC1), R31.2
ser: IC1.17 ((PCINT3/OC2A/MOSI)PB3), P9.1
start: IC1.5 ((PCINT19/OC2B/INT1)PD3), P6.3
stop: IC1.4 ((PCINT18/INT0)PD2), P6.2
up: IC1.6 ((PCINT20/XCK/T0)PD4), P6.4

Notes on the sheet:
Sau mạch lọc
0-90V
(/19) 0-4.74V
0-5A
0-0.5V
0-5V
(x9.2) 0-4.6V
-(0-0.5V)
+(0-0.5V)
NTC-MF58 100K 3950 5%
90*C-10k
40*C-52.6k
